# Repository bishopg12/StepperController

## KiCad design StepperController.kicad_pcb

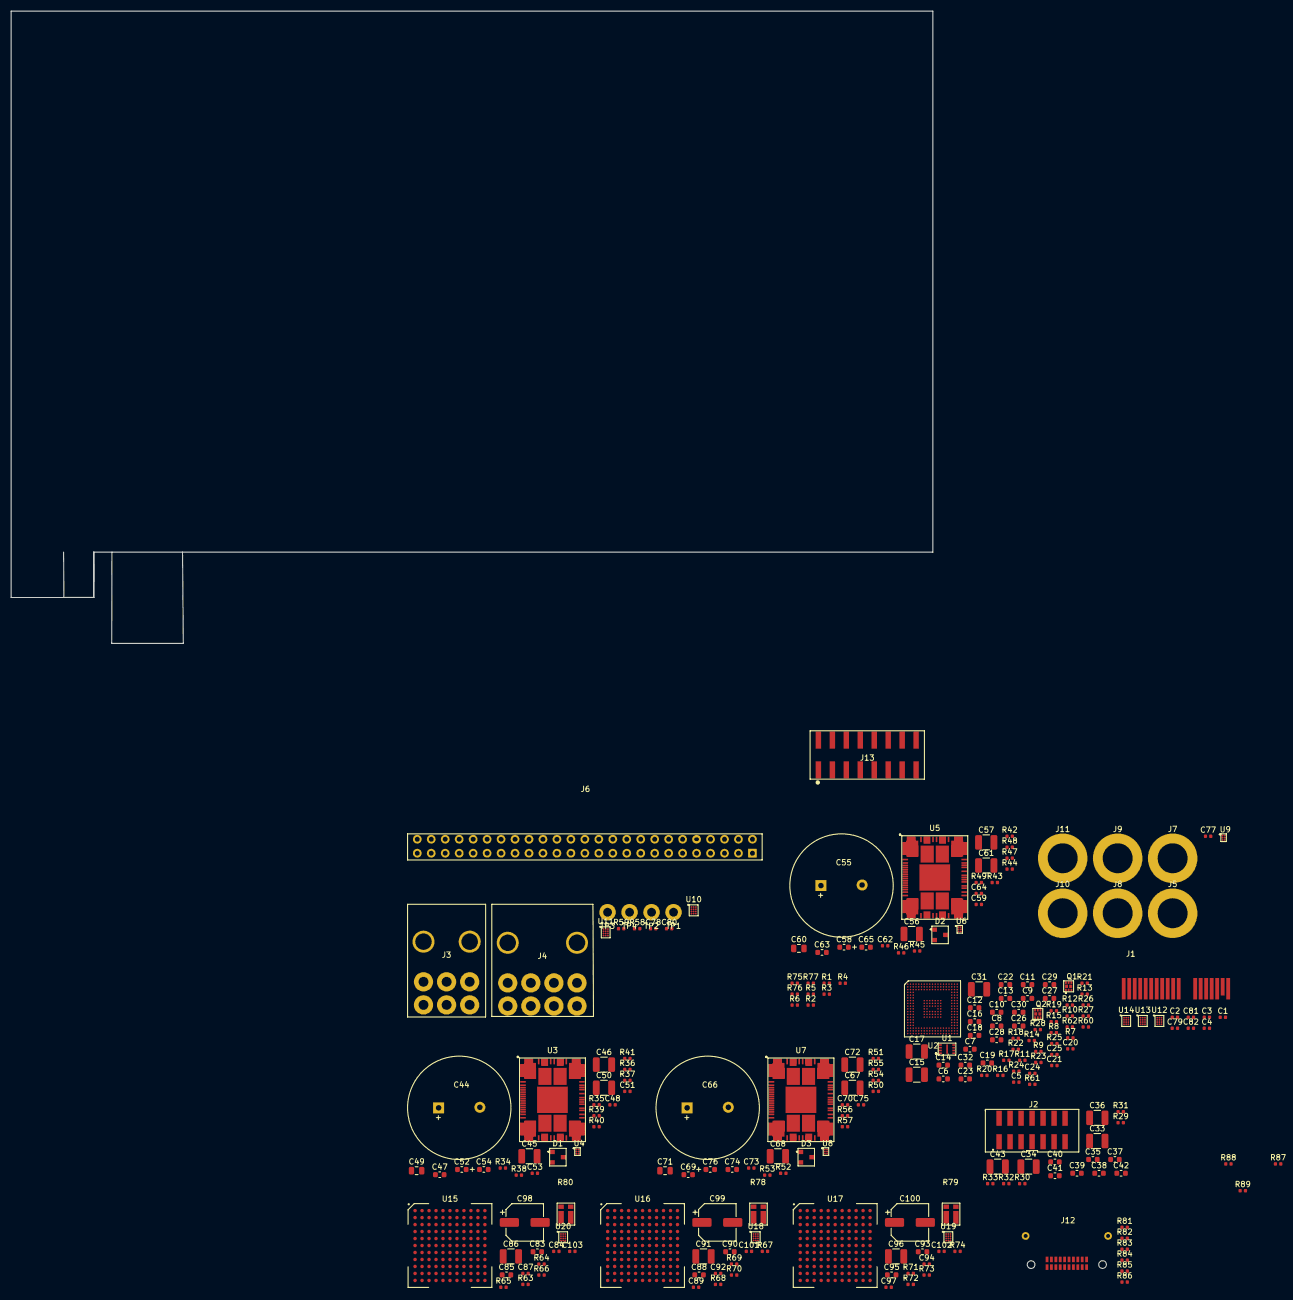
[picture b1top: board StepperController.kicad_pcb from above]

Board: 2 copper layers, 167.7 x 115.0 mm, 234 parts (0 on the bottom side), 206 nets, no tracks yet.

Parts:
C1, C2, C3, C4: swr1000000001770; C_0402_1005Metric
C5, C20, C21, C24, C25, C48, C51, C53, C59, C62, C64, C70, C73, C75, C77, C78, C80: swr100000000824; C_0402_1005Metric
C6, C8, C10, C12, C14, C16, C18, C19, C22, C26, C30, C32, C37, C38, C39, C40, C41: swr1000000001694; C_0603_1608Metric
C7, C9, C11, C13, C23, C27, C28, C29, C35, C42, C83, C85, C88, C90, C93, C95: swr1000000001553; C_0603_1608Metric
C15, C17, C31, C33, C34, C36: swr1000000001397; C_1210_3225Metric
C43: swr100000000793; C_1210_3225Metric
C44, C55, C66: swr1000000001780; UCY2C221MHD6TN
C45, C46, C56, C57, C67, C68: swr1000000001781; C_1210_3225Metric
C47, C58, C69: swr1000000001773; C_0603_1608Metric
C49, C60, C71: swr1000000001777; C_0805_2012Metric
C50, C61, C72: swr1000000001778; C_1210_3225Metric
C52, C63, C74: swr1000000001775; C_0603_1608Metric
C54, C65, C76: swr1000000001774; C_0603_1608Metric_Polarized
C79, C81, C82, C87, C92, C97, C101, C102, C103: swr1000000001742; C_0402_1005Metric
C84, C89, C94: swr1000000001522; C_0402_1005Metric
C86, C91, C96: swr100000000792; C_1210_3225Metric
C98, C99, C100: swr1000000001792; CP_Elec_6.3x6.1
D1, D2, D3: swr1000000001779; SOT-23
J1: PCIe_x1
J2: 87832-1420
J3: 457320001
J4: swr1000000001790; 455860005
J5, J7, J8, J9, J10, J11: swr1000000001726; 575-4
J6: swr1000000001789; IPT1-125-01-L-D-RA
J12: swr1000000001794; TEM-110-02-DH1-F-D-A
J13: swr1000000001795; 61031621121
Q1, Q2: swr1000000001776; FDME1024NZT
R1, R2, R3, R4, R5, R6, R29, R58, R59, R75, R76, R77, R81, R82, R83, R84, R85, R86: swr1000000001169; R_0402_1005Metric
R7, R8, R9, R10, R11, R12, R13, R14, R15, R16, R17, R18, R19, R20, R21, R22, R23, R24, R30, R39, R47, R55, R60, R61, R62: swr100000000886; R_0402_1005Metric
R25, R26, R27, R37, R45, R53, R64, R68, R72: swr1000000001398; R_0402_1005Metric
R28: swr100000000941; R_0402_1005Metric
R31, R33: swr1000000001131; R_0402_1005Metric
R32: swr100000000998; R_0402_1005Metric
R34, R38, R42, R46, R50, R54, R87, R88, R89: swr1000000001400; R_0402_1005Metric
R35, R43, R51: swr1000000001278; R_0402_1005Metric
R36, R44, R52: swr1000000001082; R_0402_1005Metric
R40, R41, R48, R49, R56, R57: swr1000000001234; R_0402_1005Metric
R63, R67, R71: swr1000000001223; R_0402_1005Metric
R65, R69, R73: swr1000000001282; R_0402_1005Metric
R66, R70, R74: swr1000000001114; R_0402_1005Metric
R78, R79, R80: swr1000000001793; R_W1206_Current_Sense
TP1, TP2, TP3, TP4: 5011
U1: swr1000000001767; USON8_3x2
U2: swr1000000001766; Xilinx_CPG238
U3, U5, U7: swr1000000001771; POWERSTEP01
U4, U6, U8, U9: swr1000000001755; 6-UFBGA
U10, U11, U12, U13, U14, U18, U19, U20: swr1000000001787; TI_12-DSBGA_(1.65x1.39)
U15, U16, U17: swr1000000001791; BGA-121_11x11_15.0x15.0mm

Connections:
+3V3: C5.1, C6.1, C7.1, C8.1, C9.1, C10.1, C11.1, C12.1, C13.1, C14.1, C15.1, C16.1, C17.1, C18.1, C19.1, C22.1, C23.1, C26.1, C27.1, C30.1, C31.1, C32.1, C33.1, C51.1, C62.1, C73.1, C77.1, C78.1, C79.1, C80.1, C81.1, C82.1, C101.1, C102.1, C103.1, J2.2, Q1.2, Q2.2, Q2.5, R1.1, R2.1, R3.1, R4.1, R5.1, R6.1, R25.1, R26.1, R27.1, R29.1, R31.1, R32.1, R33.1, R58.1, R59.1, R75.1, R76.1, R77.1, R81.1, R82.1, R83.1, R84.1, R85.1, R86.1, R88.1, R89.1, U1.8, U2.B19, U2.C14, U2.C18, U2.G12, U2.G13, U2.J7, U2.K7, U2.K12, U2.K13, U2.L7, U2.L12, U2.L13, U2.M7, U2.M8, U2.M12, U2.M13, U2.N7, U2.N8, U2.N13, U2.U12, U2.V11, U2.V13, U4.A1, U6.A1, U6.B1, U8.A1, U9.A1, U10.B1, U11.B1, U11.B3, U11.C3, U12.B1, U13.B1, U14.B1, U18.B1, U18.B3, U18.C3, U19.B1, U19.B3, U20.B1
/+12V_AUX1: R80.2, U20.D1
/+12V_AUX2: R78.2, R79.2, U18.D1, U19.D1
/+12V_AUX2_SENSE0: J4.6, R58.2, U2.B15
/+12V_AUX2_SENSE1: J4.4, R59.2, U2.C16
/DC_DC_X_AXIS_ENABLE: U2.V19, U15.L4
/DC_DC_X_AXIS_SYNC: R60.1, U15.H2
/DC_DC_Y_AXIS_ENABLE: U2.P17, U16.L4
/DC_DC_Y_AXIS_SYNC: R61.1, U16.H2
/DC_DC_Z_AXIS_ENABLE: U2.R17, U17.L4
/DC_DC_Z_AXIS_SYNC: R62.1, U17.H2
/FPGA/FPGA_IO/CCLK: R30.2, U1.6
/FPGA/FPGA_IO/EEPROM_IO0: R7.2, R21.2
/FPGA/FPGA_IO/EEPROM_IO1: R8.2, R22.2
/FPGA/FPGA_IO/EEPROM_IO2: R9.2, R23.2
/FPGA/FPGA_IO/EEPROM_IO3: R10.2, R24.2
/FPGA/FPGA_IO/EEPROM_~CS: R11.2, U1.1
/FPGA/FPGA_IO/MGTAVCC: C21.1, C25.1, C29.1, U2.C1, U2.E1, U2.G9, U2.H9
/FPGA/FPGA_IO/MGTAVTT: C20.1, C24.1, C28.1, R28.1, U2.B1, U2.C5, U2.E2, U2.G7
/FPGA/FPGA_Power_Ground_Config/TCK: J2.6, R29.2, U2.C8
/FPGA/FPGA_Power_Ground_Config/TDI: J2.10, U2.W11
/FPGA/FPGA_Power_Ground_Config/TDO: J2.8, U2.V10
/FPGA/FPGA_Power_Ground_Config/TMS: J2.4, U2.W10
/FP_GPIO_0: J12.12, U2.U3
/FP_GPIO_1: J12.11, U2.U2
/FP_GPIO_2: J12.14, U2.U4
/FP_GPIO_3: J12.13, U2.V3
/FP_GPIO_4: J12.16, U2.V4
/FP_GPIO_5: J12.15, U2.W4
/FP_GPIO_6: J12.18, U2.W3
/FP_GPIO_7: J12.17, U2.W2
/PCIe/+3.3VAux_Bus_Conn: J1.B10, U14.D1
/PCIe/+3.3V_Bus_Conn: J1.A9, J1.A10, J1.B8, U13.D1
/PCIe/+12V_Bus_Conn: J1.A2, J1.A3, J1.B1, J1.B2, J1.B3, U12.D1
/PCIe/PER0_CAP_N: C4.1, J1.A17
/PCIe/PER0_CAP_P: C2.1, J1.A16
/PCIe/REFCLK_CAP_N: C3.1, J1.A14
/PCIe/REFCLK_CAP_P: C1.1, J1.A13
/PER_N: C4.2, U2.D1
/PER_P: C2.2, U2.D2
/PET_N: J1.B15, U2.A4
/PET_P: J1.B14, U2.B4
/POWER_MON_SCL: U2.B16, U10.A1, U11.A1, U12.A1, U12.C3, U13.A1, U14.A1, U14.B3
/POWER_MON_SDA: U2.A16, U10.A2, U11.A2, U12.A2, U13.A2, U13.B3, U14.A2
/POWER_MON_~ALERT: U2.C15, U10.A3, U11.A3, U12.A3, U13.A3, U14.A3
/POWER_SCL: R75.2, U2.B18, U18.A1, U19.A1, U20.A1
/POWER_SDA: R76.2, U2.A18, U18.A2, U19.A2, U20.A2
/POWER_~ALERT: R77.2, U2.C17, U18.A3, U19.A3, U20.A3
/REFCLK_N: C3.2, U2.A8
/REFCLK_P: C1.2, U2.B8
/SMCLK: J1.B5, Q2.3, Q2.8
/SMDAT: J1.B6, Q1.6, Q1.7
/SW: J12.1, R87.1, U3.18, U5.18, U7.18
/TMP_SCL: R1.2, U2.A17, U4.B2, U6.B2, U8.B1, U8.B2, U9.B2
/TMP_SDA: R3.2, U2.A14, U4.C2, U6.C2, U8.C2, U9.B1, U9.C2
/TMP_~ALERT: R5.2, U2.A15, U4.C1, U6.C1, U8.C1, U9.C1
/VCCAUX: C34.1, C35.1, C37.1, C39.1, U2.H13, U2.J13
/VCCINT: C40.1, C41.1, C42.1, C43.1, U2.G10, U2.H10, U2.J10, U2.L10, U2.M10, U2.N10
/VCC_BRAM: C36.1, C38.1, U2.M11, U2.N11
/X_AXIS_OUTA1: J6.1, J6.3, J6.5, J6.7, U3.38, U3.42, U3.53, U3.EPAD4
/X_AXIS_OUTA2: J6.9, J6.11, J6.13, J6.15, U3.22, U3.33, U3.37
/X_AXIS_OUTB1: J6.2, J6.4, J6.6, J6.8, U3.65, U3.76, U3.80, U3.EPAD7
/X_AXIS_OUTB2: J6.10, J6.12, J6.14, J6.16, U3.7, U3.81, U3.85, U3.EPAD8
/X_AXIS_SDI: R12.2, U3.12
/X_AXIS_SDO: R39.2, U2.G18
/X_AXIS_STCK: U2.H19, U3.17
/X_AXIS_VS: C44.1, C45.1, C46.1, C86.1, C98.1, D1.1, J9.1, R35.1, R38.1, R65.1, U3.1, U3.2, U3.3, U3.4, U3.5, U3.6, U3.23, U3.24, U3.25, U3.26, U3.27, U3.28, U3.29, U3.30, U3.31, U3.32, U3.43, U3.44, U3.45, U3.46, U3.47, U3.48, U3.49, U3.50, U3.51, U3.52, U3.55, U3.66, U3.67, U3.68, U3.69, U3.70, U3.71, U3.72, U3.73, U3.74, U3.75, U3.86, U3.87, U3.88, U3.89, U3.EPAD1, U3.EPAD2, U3.EPAD5, U3.EPAD6, U15.A1, U15.A2, U15.A3, U15.A4, U15.A5, U15.A6, U15.B1, U15.B2, U15.B3, U15.B4, U15.B5, U15.B6, U15.C1, U15.C2, U15.C3, U15.C4, U15.C5, U15.C6
/X_AXIS_~BUSY~_SYNC: R41.2, U2.F17, U3.15
/X_AXIS_~CS: R13.2, U3.10
/X_AXIS_~FLAG: R40.2, U2.H18, U3.16
/X_ENDSTOP_0: J12.5, R81.2, U2.T17
/X_ENDSTOP_1: J12.6, R86.2, U2.T18
/Y_AXIS_OUTA1: J6.17, J6.19, J6.21, J6.23, U5.38, U5.42, U5.53, U5.EPAD4
/Y_AXIS_OUTA2: J6.25, J6.27, J6.29, J6.31, U5.22, U5.33, U5.37
/Y_AXIS_OUTB1: J6.18, J6.20, J6.22, J6.24, U5.65, U5.76, U5.80, U5.EPAD7
/Y_AXIS_OUTB2: J6.26, J6.28, J6.30, J6.32, U5.7, U5.81, U5.85, U5.EPAD8
/Y_AXIS_SDI: R15.2, U5.12
/Y_AXIS_SDO: R47.2, U2.K19
/Y_AXIS_STCK: U2.N18, U5.17
/Y_AXIS_VS: C55.1, C56.1, C57.1, C91.1, C99.1, D2.1, J10.1, R43.1, R46.1, R69.1, U5.1, U5.2, U5.3, U5.4, U5.5, U5.6, U5.23, U5.24, U5.25, U5.26, U5.27, U5.28, U5.29, U5.30, U5.31, U5.32, U5.43, U5.44, U5.45, U5.46, U5.47, U5.48, U5.49, U5.50, U5.51, U5.52, U5.55, U5.66, U5.67, U5.68, U5.69, U5.70, U5.71, U5.72, U5.73, U5.74, U5.75, U5.86, U5.87, U5.88, U5.89, U5.EPAD1, U5.EPAD2, U5.EPAD5, U5.EPAD6, U16.A1, U16.A2, U16.A3, U16.A4, U16.A5, U16.A6, U16.B1, U16.B2, U16.B3, U16.B4, U16.B5, U16.B6, U16.C1, U16.C2, U16.C3, U16.C4, U16.C5, U16.C6
/Y_AXIS_~BUSY~_SYNC: R49.2, U2.M19, U5.15
/Y_AXIS_~CS: R16.2, U5.10
/Y_AXIS_~FLAG: R48.2, U2.L19, U5.16
/Y_ENDSTOP_0: J12.7, R82.2, U2.U17
/Y_ENDSTOP_1: J12.8, R85.2, U2.U18
/Z_AXIS_OUTA1: J6.33, J6.35, J6.37, J6.39, U7.38, U7.42, U7.53, U7.EPAD4
/Z_AXIS_OUTA2: J6.41, J6.43, J6.45, J6.47, U7.22, U7.33, U7.37
/Z_AXIS_OUTB1: J6.34, J6.36, J6.38, J6.40, U7.65, U7.76, U7.80, U7.EPAD7
/Z_AXIS_OUTB2: J6.42, J6.44, J6.46, J6.48, U7.7, U7.81, U7.85, U7.EPAD8
/Z_AXIS_SDI: R18.2, U7.12
/Z_AXIS_SDO: R55.2, U2.L17
/Z_AXIS_STCK: U2.P18, U7.17
/Z_AXIS_VS: C66.1, C67.1, C68.1, C96.1, C100.1, D3.1, J11.1, R51.1, R54.1, R73.1, U7.1, U7.2, U7.3, U7.4, U7.5, U7.6, U7.23, U7.24, U7.25, U7.26, U7.27, U7.28, U7.29, U7.30, U7.31, U7.32, U7.43, U7.44, U7.45, U7.46, U7.47, U7.48, U7.49, U7.50, U7.51, U7.52, U7.55, U7.66, U7.67, U7.68, U7.69, U7.70, U7.71, U7.72, U7.73, U7.74, U7.75, U7.86, U7.87, U7.88, U7.89, U7.EPAD1, U7.EPAD2, U7.EPAD5, U7.EPAD6, U17.A1, U17.A2, U17.A3, U17.A4, U17.A5, U17.A6, U17.B1, U17.B2, U17.B3, U17.B4, U17.B5, U17.B6, U17.C1, U17.C2, U17.C3, U17.C4, U17.C5, U17.C6
/Z_AXIS_~BUSY~_SYNC: R57.2, U2.P19, U7.15
/Z_AXIS_~CS: R19.2, U7.10
/Z_AXIS_~FLAG: R56.2, U2.N19, U7.16
/Z_ENDSTOP_0: J12.9, R83.2, U2.W17
/Z_ENDSTOP_1: J12.10, R84.2, U2.W18
/~PERST: J1.A11, Q2.6, Q2.7
GND: C5.2, C6.2, C7.2, C8.2, C9.2, C10.2, C11.2, C12.2, C13.2, C14.2, C15.2, C16.2, C17.2, C18.2, C19.2, C20.2, C21.2, C22.2, C23.2, C24.2, C25.2, C26.2, C27.2, C28.2, C29.2, C30.2, C31.2, C32.2, C33.2, C34.2, C35.2, C36.2, C37.2, C38.2, C39.2, C40.2, C41.2, C42.2, C43.2, C44.2, C45.2, C46.2, C47.2, C48.2, C51.2, C52.2, C53.2, C54.2, C55.2, C56.2, C57.2, C58.2, C59.2, C62.2, C63.2, C64.2, C65.2, C66.2, C67.2, C68.2, C69.2, C70.2, C73.2, C74.2, C75.2, C76.2, C77.2, C78.2, C79.2, C80.2, C81.2, C82.2, C83.2, C84.2, C85.2, C86.2, C87.2, C88.2, C89.2, C90.2, C91.2, C92.2, C93.2, C94.2, C95.2, C96.2, C97.2, C98.2, C99.2, C100.2, C101.2, C102.2, C103.2, J1.A4, J1.A12, J1.A15, J1.A18, J1.B4, J1.B7, J1.B13, J1.B16, J1.B18, J2.1, J2.3, J2.5, J2.7, J2.9, J2.11, J2.13, J4.5, J4.7, J4.8, J5.1, J7.1, J8.1, J12.19, J12.20, R36.2, R44.2, R52.2, R63.2, R66.2, R67.2, R70.2, R71.2, R74.2, TP1.1, TP2.1, TP3.1, TP4.1, U1.4, U2.A1, U2.A3, U2.A5, U2.A7, U2.A9, U2.A19, U2.B3, U2.B5, U2.B7, U2.B9, U2.B14, U2.C2, U2.C3, U2.C4, U2.C6, U2.C9, U2.C10, U2.C19, U2.D3, U2.E3, U2.F1, U2.F2, U2.F3, U2.F18, U2.G8, U2.G11, U2.H7, U2.H8, U2.H11, U2.H12, U2.J2, U2.J8, U2.J9, U2.J11, U2.J12, U2.J18, U2.K8, U2.L8, U2.L9, U2.L11, U2.M2, U2.M9, U2.M18, U2.N9, U2.N12, U2.R2, U2.R18, U2.U13, U2.V2, U2.V5, U2.V8, U2.V12, U2.V15, U2.V18, U2.W1, U2.W13, U2.W19, U3.8, U3.9, U3.20, U3.21, U3.34, U3.35, U3.36, U3.39, U3.40, U3.41, U3.59, U3.77, U3.78, U3.79, U3.82, U3.83, U3.84, U3.EPAD9, U3.EPAD10, U3.EPAD11, U3.EPAD12, U3.EPAD13, U4.A2, U4.B1, U5.8, U5.9, U5.20, U5.21, U5.34, U5.35, U5.36, U5.39, U5.40, U5.41, U5.59, U5.77, U5.78, U5.79, U5.82, U5.83, U5.84, U5.EPAD9, U5.EPAD10, U5.EPAD11, U5.EPAD12, U5.EPAD13, U6.A2, U7.8, U7.9, U7.20, U7.21, U7.34, U7.35, U7.36, U7.39, U7.40, U7.41, U7.59, U7.77, U7.78, U7.79, U7.82, U7.83, U7.84, U7.EPAD9, U7.EPAD10, U7.EPAD11, U7.EPAD12, U7.EPAD13, U8.A2, U9.A2, U10.B3, U10.C1, U10.C3, U11.C1, U12.B3, U12.C1, U13.C1, U13.C3, U14.C1, U14.C3, U15.A7, U15.A8, U15.A9, U15.A10, U15.A11, U15.B7, U15.B8, U15.B9, U15.B10, U15.B11, U15.C7, U15.C8, U15.C9, U15.C10, U15.C11, U15.D2, U15.D3, U15.D4, U15.D5, U15.D6, U15.D7, U15.D8, U15.D9, U15.D10, U15.D11, U15.E1, U15.E2, U15.E3, U15.E4, U15.E5, U15.E6, U15.E7, U15.E8, U15.E9, U15.E10, U15.E11, U15.F2, U15.F3, U15.F4, U15.F5, U15.F6, U15.F7, U15.F8, U15.F9, U15.G3, U15.G4, U15.G5, U15.G6, U15.G7, U15.G8, U15.G9, U15.H3, U15.H4, U15.H5, U15.H6, U15.H7, U15.H8, U15.H9, U15.J3, U15.J4, U15.J5, U15.J6, U15.J7, U15.J8, U15.J9, U15.K3, U15.K4, U15.K5, U15.K6, U15.K7, U15.K8, U15.K9, U15.L1, U15.L5, U15.L6, U15.L7, U15.L8, U16.A7, U16.A8, U16.A9, U16.A10, U16.A11, U16.B7, U16.B8, U16.B9, U16.B10, U16.B11, U16.C7, U16.C8, U16.C9, U16.C10, U16.C11, U16.D2, U16.D3, U16.D4, U16.D5, U16.D6, U16.D7, U16.D8, U16.D9, U16.D10, U16.D11, U16.E1, U16.E2, U16.E3, U16.E4, U16.E5, U16.E6, U16.E7, U16.E8, U16.E9, U16.E10, U16.E11, U16.F2, U16.F3, U16.F4, U16.F5, U16.F6, U16.F7, U16.F8, U16.F9, U16.G3, U16.G4, U16.G5, U16.G6, U16.G7, U16.G8, U16.G9, U16.H3, U16.H4, U16.H5, U16.H6, U16.H7, U16.H8, U16.H9, U16.J3, U16.J4, U16.J5, U16.J6, U16.J7, U16.J8, U16.J9, U16.K3, U16.K4, U16.K5, U16.K6, U16.K7, U16.K8, U16.K9, U16.L1, U16.L5, U16.L6, U16.L7, U16.L8, U17.A7, U17.A8, U17.A9, U17.A10, U17.A11, U17.B7, U17.B8, U17.B9, U17.B10, U17.B11, U17.C7, U17.C8, U17.C9, U17.C10, U17.C11, U17.D2, U17.D3, U17.D4, U17.D5, U17.D6, U17.D7, U17.D8, U17.D9, U17.D10, U17.D11, U17.E1, U17.E2, U17.E3, U17.E4, U17.E5, U17.E6, U17.E7, U17.E8, U17.E9, U17.E10, U17.E11, U17.F2, U17.F3, U17.F4, U17.F5, U17.F6, U17.F7, U17.F8, U17.F9, U17.G3, U17.G4, U17.G5, U17.G6, U17.G7, U17.G8, U17.G9, U17.H3, U17.H4, U17.H5, U17.H6, U17.H7, U17.H8, U17.H9, U17.J3, U17.J4, U17.J5, U17.J6, U17.J7, U17.J8, U17.J9, U17.K3, U17.K4, U17.K5, U17.K6, U17.K7, U17.K8, U17.K9, U17.L1, U17.L5, U17.L6, U17.L7, U17.L8, U18.C1, U19.C1, U19.C3, U20.B3, U20.C1, U20.C3
unnamed: C47.1, C48.1, U3.58, U3.60
unnamed: C49.1, U3.57
unnamed: C49.2, D1.2
unnamed: C50.1, U3.56
unnamed: C50.2, D1.3
unnamed: C52.1, R38.2, U3.61
unnamed: C53.1, C54.1, R40.1, R41.1, U3.13, U3.62
unnamed: C58.1, C59.1, U5.58, U5.60
unnamed: C60.1, U5.57
unnamed: C60.2, D2.2
unnamed: C61.1, U5.56
unnamed: C61.2, D2.3
unnamed: C63.1, R46.2, U5.61
unnamed: C64.1, C65.1, R48.1, R49.1, U5.13, U5.62
unnamed: C69.1, C70.1, U7.58, U7.60
unnamed: C71.1, U7.57
unnamed: C71.2, D3.2
unnamed: C72.1, U7.56
unnamed: C72.2, D3.3
unnamed: C74.1, R54.2, U7.61
unnamed: C75.1, C76.1, R56.1, R57.1, U7.13, U7.62
unnamed: C83.1, C84.1, C85.1, R80.3, U15.F10, U15.F11, U15.G10, U15.G11, U15.H10, U15.H11, U15.J10, U15.J11, U15.K10, U15.K11, U15.L10, U15.L11
unnamed: C87.1, U15.K1
unnamed: C88.1, C89.1, C90.1, R78.3, U16.F10, U16.F11, U16.G10, U16.G11, U16.H10, U16.H11, U16.J10, U16.J11, U16.K10, U16.K11, U16.L10, U16.L11
unnamed: C92.1, U16.K1
unnamed: C93.1, C94.1, C95.1, R79.3, U17.F10, U17.F11, U17.G10, U17.G11, U17.H10, U17.H11, U17.J10, U17.J11, U17.K10, U17.K11, U17.L10, U17.L11
unnamed: C97.1, U17.K1
unnamed: J1.A1, J1.B17
unnamed: J3.1, J3.2, J3.3, U10.D1
unnamed: J3.4, J3.5, J3.6
unnamed: J4.1, J4.2, J4.3, U11.D1
unnamed: J12.3, R88.2
unnamed: J12.4, R89.2
unnamed: J13.1, U2.H1
unnamed: J13.2, U2.J1
unnamed: J13.3, U2.H2
unnamed: J13.4, U2.K2
unnamed: J13.5, U2.H3
unnamed: J13.6, U2.K1
unnamed: J13.7, U2.G1
unnamed: J13.8, U2.J3
unnamed: J13.9, U2.N1
unnamed: J13.10, U2.K3
unnamed: J13.11, U2.P2
unnamed: J13.12, U2.L3
unnamed: J13.13, U2.N2
unnamed: J13.14, U2.L2
unnamed: J13.15, U2.M1
unnamed: J13.16, U2.L1
unnamed: Q1.1, R25.2, U2.G3
unnamed: Q2.1, R26.2, U2.G2
unnamed: Q2.4, R27.2, U2.V1
unnamed: R7.1, U2.D18
unnamed: R8.1, U2.D19
unnamed: R9.1, U2.E19
unnamed: R10.1, U2.F19
unnamed: R11.1, U2.G19
unnamed: R12.1, U2.D17
unnamed: R13.1, U2.E17
unnamed: R14.1, U2.E18
unnamed: R15.1, U2.H17
unnamed: R16.1, U2.J17
unnamed: R17.1, U2.J19
unnamed: R18.1, U2.K18
unnamed: R19.1, U2.L18
unnamed: R20.1, U2.K17
unnamed: R21.1, U1.5
unnamed: R22.1, U1.2
unnamed: R23.1, U1.3
unnamed: R24.1, U1.7
unnamed: R28.2, U2.C7
unnamed: R30.1, U2.C11
unnamed: R31.2, U2.U10
unnamed: R32.2, U2.U11
unnamed: R33.2, U2.W12
unnamed: R34.1, R37.1, U3.63
unnamed: R35.2, R36.1, U3.54
unnamed: R39.1, U3.14
unnamed: R42.1, R45.1, U5.63
unnamed: R43.2, R44.1, U5.54
unnamed: R47.1, U5.14
unnamed: R50.1, R53.1, U7.63
unnamed: R51.2, R52.1, U7.54
unnamed: R55.1, U7.14
unnamed: R60.2, U2.R19
unnamed: R61.2, U2.T19
unnamed: R62.2, U2.U19
unnamed: R63.1, U15.H1
unnamed: R64.1, U15.F1
unnamed: R64.2, U15.G2
unnamed: R65.2, R66.1, U15.J1
unnamed: R67.1, U16.H1
unnamed: R68.1, U16.F1
unnamed: R68.2, U16.G2
unnamed: R69.2, R70.1, U16.J1
unnamed: R71.1, U17.H1
unnamed: R72.1, U17.F1
unnamed: R72.2, U17.G2
unnamed: R73.2, R74.1, U17.J1
unnamed: R78.1, U16.L9, U18.D3
unnamed: R78.4, U18.D2
unnamed: R79.1, U17.L9, U19.D3
unnamed: R79.4, U19.D2
unnamed: R80.1, U15.L9, U20.D3
unnamed: R80.4, U20.D2
unnamed: R87.2, U2.V16

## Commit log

2021-02-06 Added power supply sense resistors
2021-02-10 Finalize non power connections
2021-02-15 Initial power plumbing
2021-09-12 Add missing files
